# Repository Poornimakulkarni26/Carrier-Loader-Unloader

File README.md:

# Carrier Tray Loader / Unloader Controller

An RP2040-based industrial PCB designed to automate carrier tray handling for PnP machines — eliminating the need for a human operator to manually feed and collect trays during production runs.

## The Problem

PnP machines require a continuous supply of carrier trays to place components into. Without automation, an operator must stand at the machine full-time — manually loading empty trays one by one and collecting filled ones. This is wasteful, error-prone, and ties up a person for the entire production run.

## The Solution

This controller board powers two machines that work together:

**Loader** — Operator loads a stack of 5–10 empty trays at once. The machine automatically feeds one tray at a time onto the conveyor when the pick-and-place machine is ready, then steps down to the next tray in the stack.

**Unloader** — Collects filled trays returning from the PnP machine, stacks them, and steps up to make room for the next incoming tray — building a neat stack of completed trays without any human intervention.

## How It Works

```
        [Loader Stack]                    [Unloader Stack]
        ┌──────────┐                      ┌──────────┐
        │  Tray 5  │                      │  Tray 5  │ ← collecting
        │  Tray 4  │                      │  Tray 4  │
        │  Tray 3  │   → conveyor →       │  Tray 3  │
        │  Tray 2  │                      │  Tray 2  │
        │  Tray 1  │ ← feeding out        │  Tray 1  │
        └──────────┘                      └──────────┘
        Stepper: X (in/out)               Stepper: X (in/out)
        Stepper: Z (up/down)              Stepper: Z (up/down)
```

- **X-axis stepper** — pushes tray out onto conveyor (loader) / pulls tray in from conveyor (unloader)
- **Z-axis stepper** — moves platform up or down to align next tray with conveyor height
- **Proximity sensors** — detect tray presence at feed/collect position
- **Inductive sensors** — detect platform position for homing and limit detection
- **24V digital inputs** — industrial-standard signal levels for all sensors

## Hardware

| Parameter | Value |
|---|---|
| Microcontroller | RP2040 (Dual-core Arm Cortex-M0+, 133 MHz) |
| Digital Inputs | 24V industrial standard (proximity + inductive sensors) |
| Digital Outputs | Stepper motor driver signals |
| Motion axes | X (tray in/out), Z (platform up/down) |
| Tray capacity | 5–10 trays per load |
| EDA Tool | KiCad |

## Sensors Used

- **Proximity sensors** — tray presence detection at feed and collect positions
- **Inductive sensors** — metal platform position detection, homing, and end-stop limits

## Board Images

## Repository Structure

```
├── README.md
├── .gitignore
├── Carrier_traySchematic.kicad_pro     # Main project file
├── Carrier_traySchematic.kicad_sch     # Schematic
├── Carrier_traySchematic.kicad_pcb     # PCB layout
├── Carrier_traySchematicPCB.kicad_pro  # PCB project file
├── Carrier_traySchematicPCB.kicad_pcb  # PCB layout variant
├── CTG-Topview.png                     # Board top view render
└── CTG-frontview.png                   # Board front view render
```

## Getting Started

1. Install [KiCad](https://www.kicad.org/) (v7+ recommended)
2. Clone this repository:
   ```bash
   git clone https://github.com/Poornimakulkarni26/loader-unloader-pcb.git
   ```
3. Open `Carrier_traySchematic.kicad_pro` in KiCad

## Key Design Decisions

- **RP2040 chosen** for its dual-core architecture — one core handles motion control timing, the other handles sensor polling and logic, keeping stepper pulses jitter-free
- **24V DI inputs** to interface directly with standard industrial sensors without extra signal conditioning boards
- **Dedicated stepper outputs** for independent X and Z axis control with configurable microstepping

## Impact

- Eliminated full-time operator requirement at loader/unloader stations
- Allows batch loading of 5–10 trays, freeing the operator for other tasks
- Consistent tray feeding speed improves Pnp throughput
- Reduced tray misalignment errors compared to manual feeding

## Author

**Poornima Kulkarni**
Embedded Systems & Industrial Automation Engineer

- GitHub: [@Poornimakulkarni26](https://github.com/Poornimakulkarni26)

## License

This project is open-source under the [MIT License](LICENSE).

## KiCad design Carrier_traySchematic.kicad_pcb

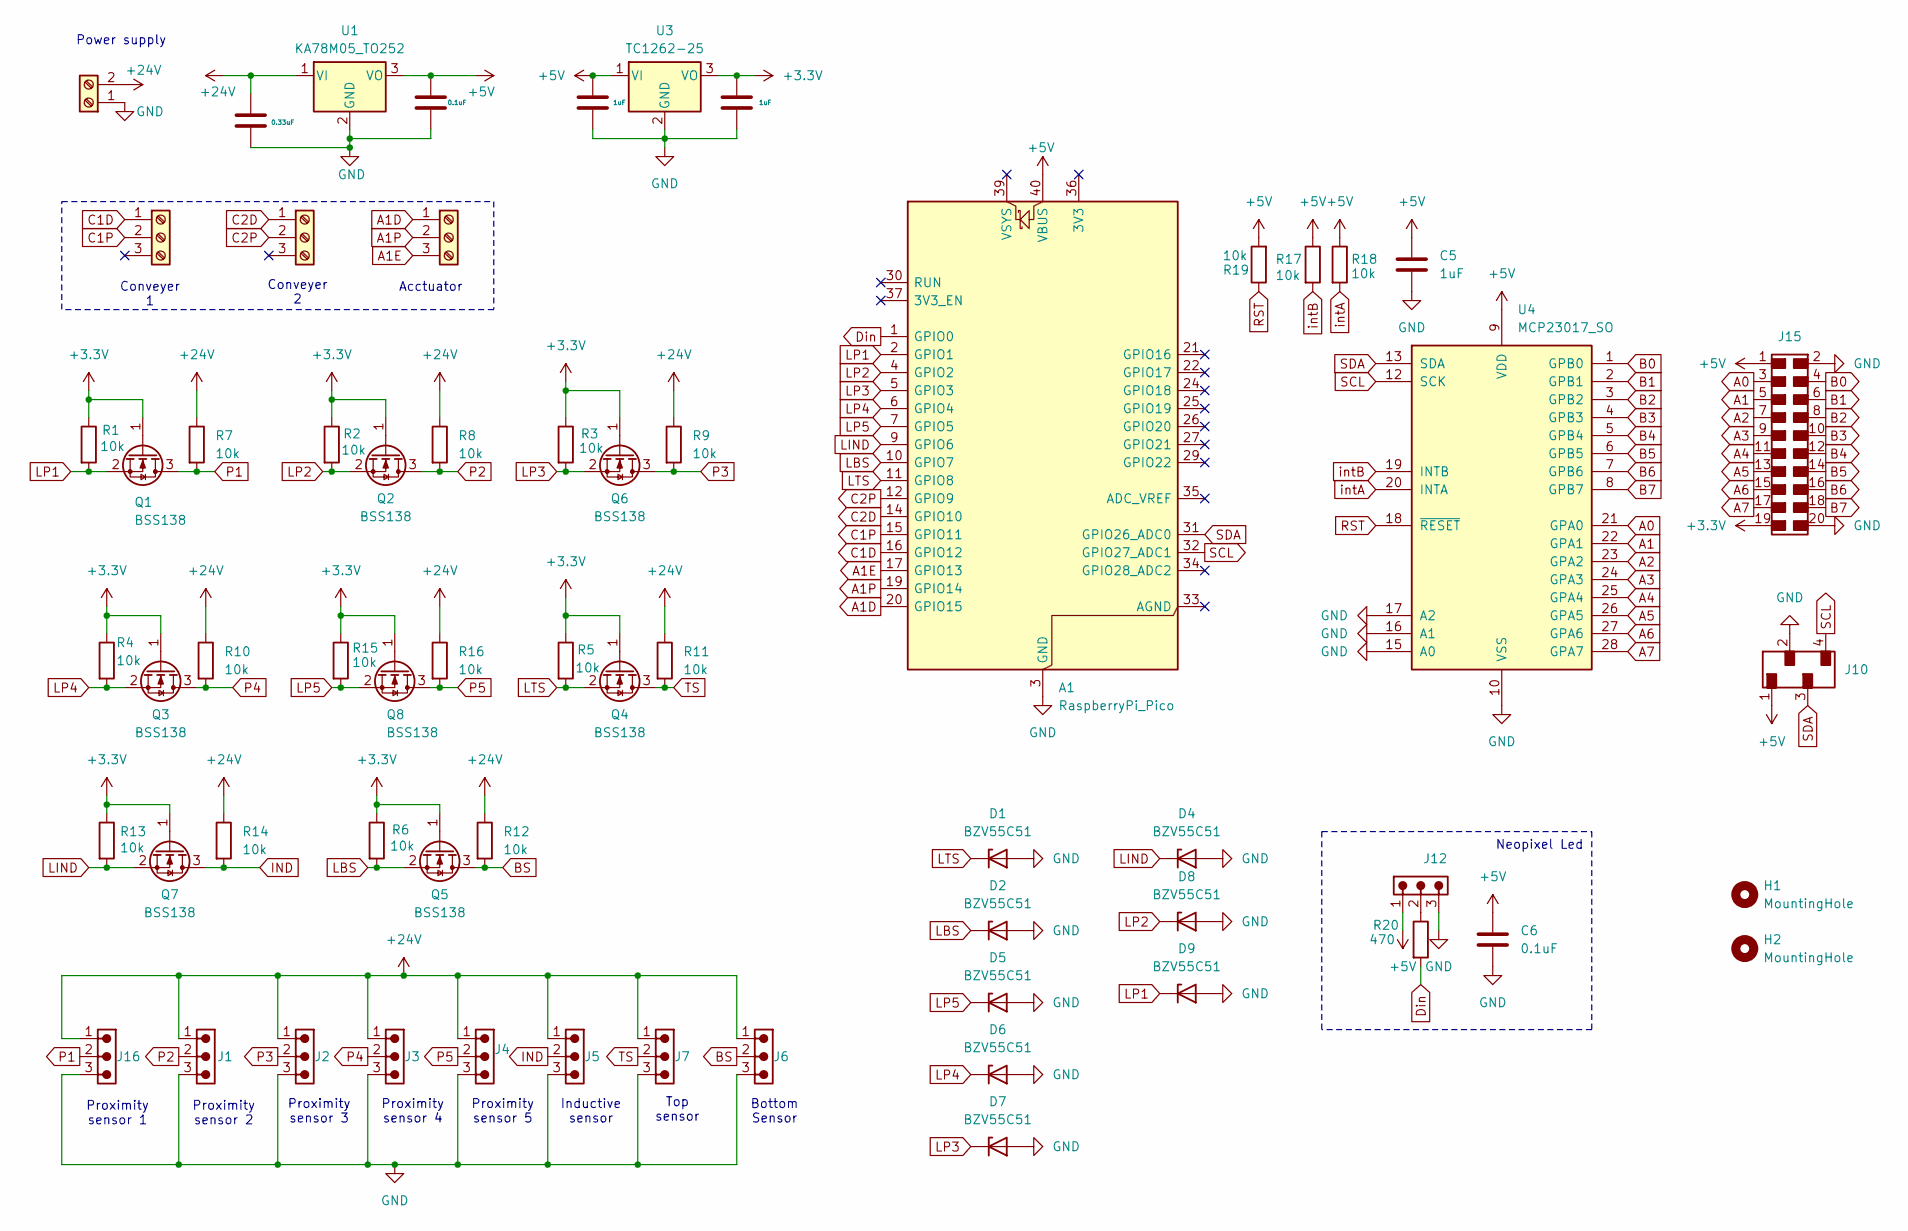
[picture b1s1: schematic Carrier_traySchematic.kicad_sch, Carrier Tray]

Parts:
A1: RaspberryPi_Pico; RaspberryPi_Pico_Common_Unspecified
C1: 0.33uF; C_0603_1608Metric_Pad1.08x0.95mm_HandSolder
C2, C6: 0.1uF; C_0603_1608Metric_Pad1.08x0.95mm_HandSolder
C3, C4, C5: 1uF; C_0603_1608Metric_Pad1.08x0.95mm_HandSolder
D1, D2, D4, D5, D6, D7, D8, D9: BZV55C51; D_MiniMELF
H1, H2: MountingHole; MountingHole_3.2mm_M3_DIN965_Pad
J1, J2, J3, J4, J5, J6, J7, J16: 68800311622; J_Wurth_WR-WTB_68800311622; Working Voltage (V (AC)) 250
J8, J9, J14: Screw_Terminal_01x03; TerminalBlock_Xinya_XY308-2.54-3P_1x03_P2.54mm_Horizontal
J10: 61000418221; J_Wurth_WR-PHD_61300411121
J11: Screw_Terminal_01x02; TerminalBlock_MetzConnect_Type011_RT05502HBLC_1x02_P5.00mm_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
J12: 61300311121; J_Wurth_WR-PHD_61300311121
J15: 621020245821; J_Wurth_WR-PHD_61302021821
Q1, Q2, Q3, Q4, Q5, Q6, Q7, Q8: BSS138; SOT-23
R1, R2, R3, R4, R5, R6, R7, R8, R9, R10, R11, R12, R13, R14, R15, R16, R17, R18, R19: 10k; R_0603_1608Metric_Pad0.98x0.95mm_HandSolder
R20: 470; R_0603_1608Metric_Pad0.98x0.95mm_HandSolder
U1: KA78M05_TO252; TO-252-2
U3: TC1262-25; SOT-223
U4: MCP23017_SO; SOIC-28W_7.5x17.9mm_P1.27mm

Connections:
+3.3V: C3.1, J15.19, Q1.1 (G), Q2.1 (G), Q3.1 (G), Q4.1 (G), Q5.1 (G), Q6.1 (G), Q7.1 (G), Q8.1 (G), R1.1, R2.1, R3.1, R4.1, R5.1, R6.1, R13.1, R15.1, U3.3 (VO)
+5V: A1.40 (VBUS), C2.1, C4.1, C5.1, C6.1, J10.1, J12.1, J15.1, R17.1, R18.1, R19.2, U1.3 (VO), U3.1 (VI), U4.9 (VDD)
+24V: C1.1, J1.1, J2.1, J3.1, J4.1, J5.1, J6.1, J7.1, J11.2, J16.1, R7.1, R8.1, R9.1, R10.1, R11.1, R12.1, R14.1, R16.1, U1.1 (VI)
A0: J15.3, U4.21 (GPA0)
A1: J15.5, U4.22 (GPA1)
A1D: A1.20 (GPIO15), J9.1
A1E: A1.17 (GPIO13), J9.3
A1P: A1.19 (GPIO14), J9.2
A2: J15.7, U4.23 (GPA2)
A3: J15.9, U4.24 (GPA3)
A4: J15.11, U4.25 (GPA4)
A5: J15.13, U4.26 (GPA5)
A6: J15.15, U4.27 (GPA6)
A7: J15.17, U4.28 (GPA7)
B0: J15.4, U4.1 (GPB0)
B1: J15.6, U4.2 (GPB1)
B2: J15.8, U4.3 (GPB2)
B3: J15.10, U4.4 (GPB3)
B4: J15.12, U4.5 (GPB4)
B5: J15.14, U4.6 (GPB5)
B6: J15.16, U4.7 (GPB6)
B7: J15.18, U4.8 (GPB7)
BS: J6.2, Q5.3 (D), R12.2
C1D: A1.16 (GPIO12), J14.1
C1P: A1.15 (GPIO11), J14.2
C2D: A1.14 (GPIO10), J8.1
C2P: A1.12 (GPIO9), J8.2
Din: A1.1 (GPIO0), R20.2
GND: A1.3 (GND), A1.8 (GND), A1.13 (GND), A1.18 (GND), A1.23 (GND), A1.28 (GND), A1.38 (GND), C1.2, C2.2, C3.2, C4.2, C5.2, C6.2, D1.2 (A), D2.2 (A), D4.2 (A), D5.2 (A), D6.2 (A), D7.2 (A), D8.2 (A), D9.2 (A), J1.3, J2.3, J3.3, J4.3, J5.3, J6.3, J7.3, J10.2, J11.1, J12.3, J15.2, J15.20, J16.3, U1.2 (GND), U3.2 (GND), U4.10 (VSS), U4.15 (A0), U4.16 (A1), U4.17 (A2)
IND: J5.2, Q7.3 (D), R14.2
LBS: A1.10 (GPIO7), D2.1 (K), Q5.2 (S), R6.2
LIND: A1.9 (GPIO6), D4.1 (K), Q7.2 (S), R13.2
LP1: A1.2 (GPIO1), D9.1 (K), Q1.2 (S), R1.2
LP2: A1.4 (GPIO2), D8.1 (K), Q2.2 (S), R2.2
LP3: A1.5 (GPIO3), D7.1 (K), Q6.2 (S), R3.2
LP4: A1.6 (GPIO4), D6.1 (K), Q3.2 (S), R4.2
LP5: A1.7 (GPIO5), D5.1 (K), Q8.2 (S), R15.2
LTS: A1.11 (GPIO8), D1.1 (K), Q4.2 (S), R5.2
unnamed: J12.2, R20.1
P1: J16.2, Q1.3 (D), R7.2
P2: J1.2, Q2.3 (D), R8.2
P3: J2.2, Q6.3 (D), R9.2
P4: J3.2, Q3.3 (D), R10.2
P5: J4.2, Q8.3 (D), R16.2
RST: R19.1, U4.18 (~RESET)
TS: J7.2, Q4.3 (D), R11.2
intA: R18.2, U4.20 (INTA)
intB: R17.2, U4.19 (INTB)

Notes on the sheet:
Proximity sensor 2
Bottom Sensor
Power supply
Proximity sensor 1
Proximity sensor 4
Top sensor
Conveyer 1
Acctuator
Conveyer 2
Proximity sensor 3
Neopixel Led
Proximity sensor 5
Inductive sensor

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
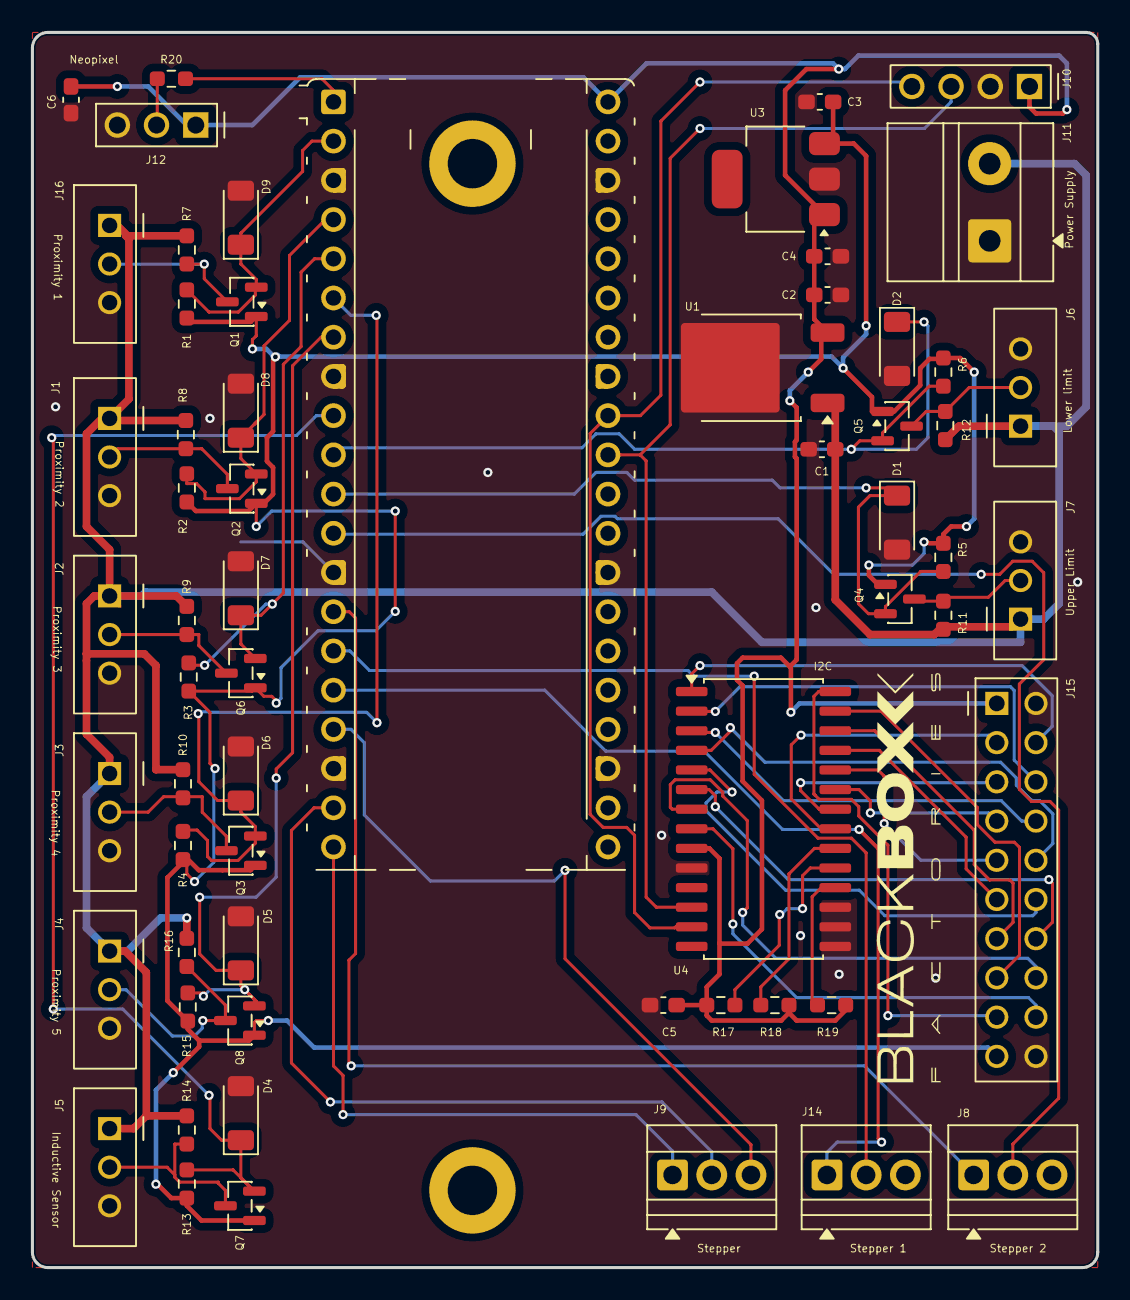
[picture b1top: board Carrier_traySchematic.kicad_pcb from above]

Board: 2 copper layers, 69.0 x 80.0 mm, 63 parts (0 on the bottom side), 50 nets.

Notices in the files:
README.md:
License: MIT
